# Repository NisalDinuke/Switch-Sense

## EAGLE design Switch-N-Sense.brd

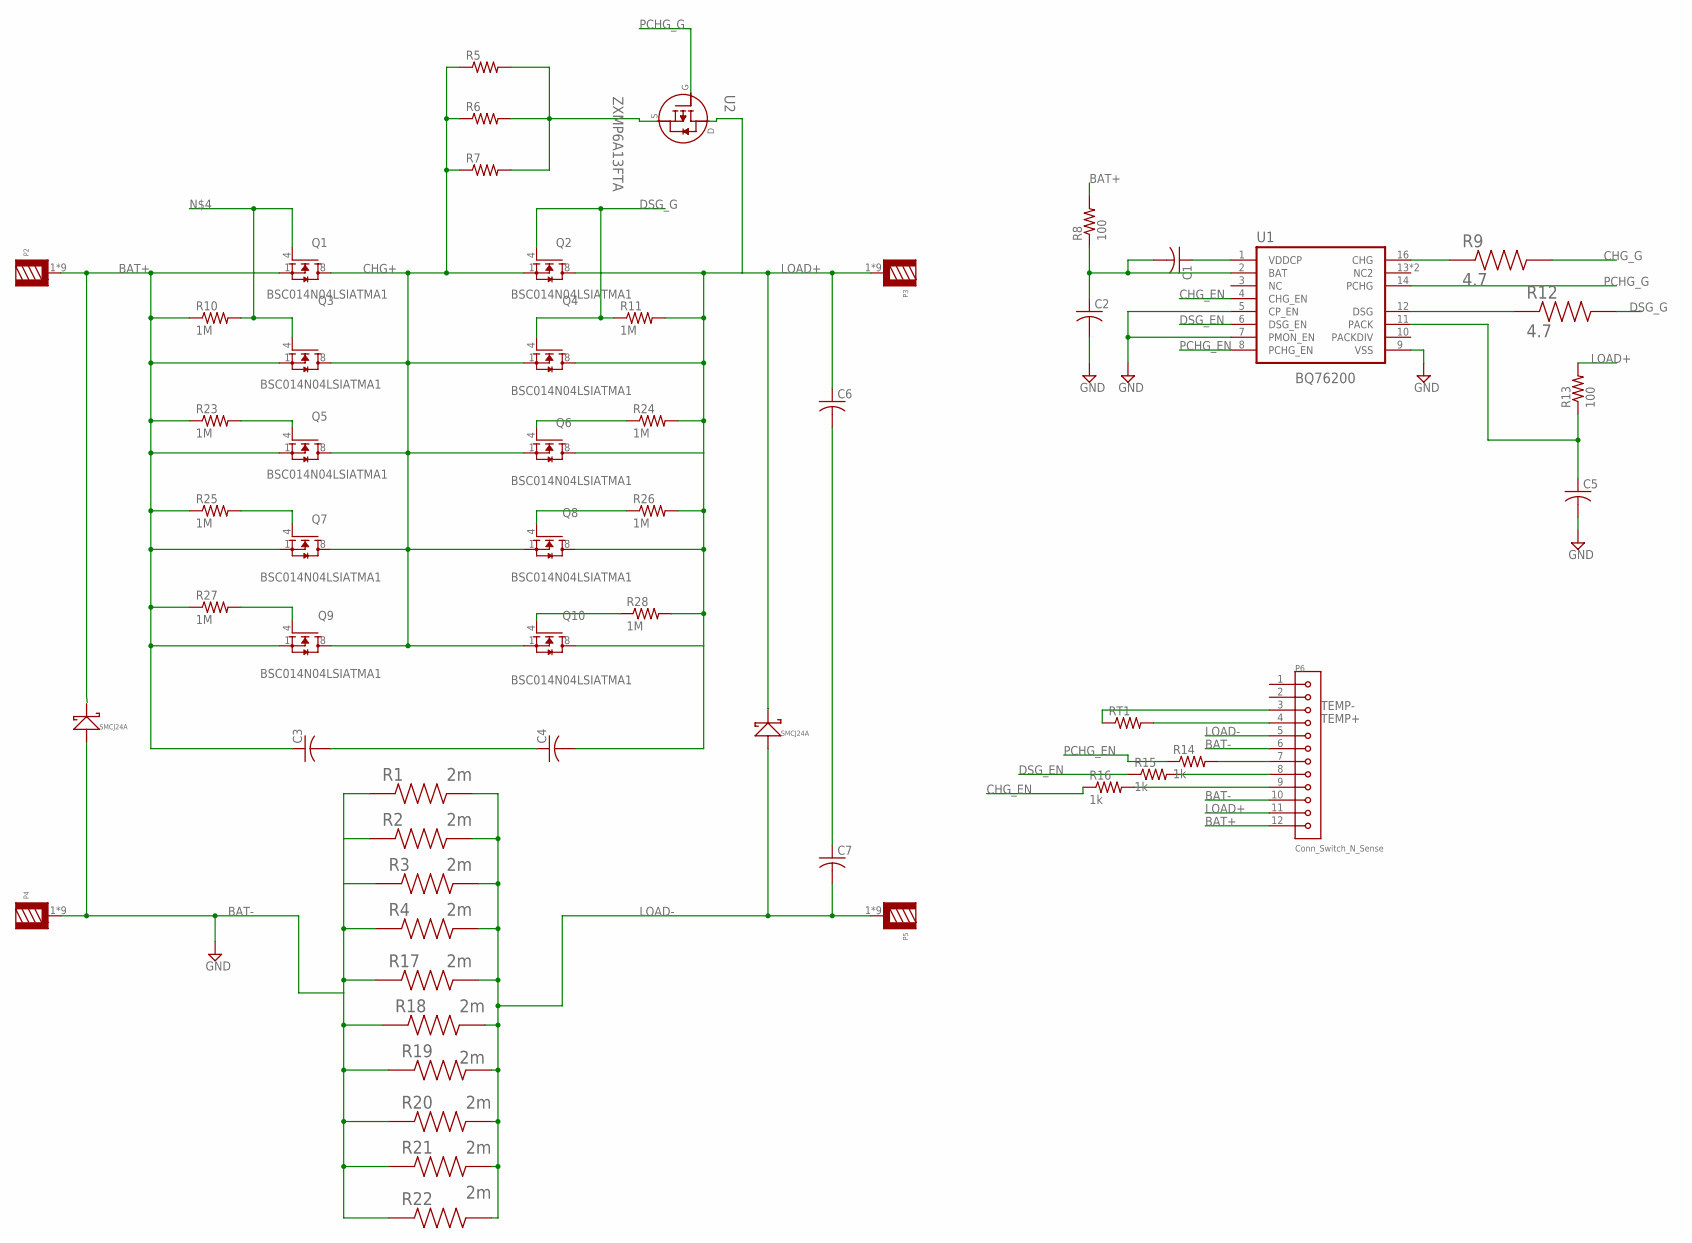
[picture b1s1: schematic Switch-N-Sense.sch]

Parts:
C1: C-USC0805; C0805
C2, C3, C4, C5, C6, C7: C-USC0603; C0603
D1, D2: SMCJ24A; DIOM794X590X262L114X305N
P2, P3, P4, P5: WP-THRBU_BLIND-HOLE_74650195; WP-THRBU_74650195
P6: Conn_Switch_N_Sense; JST_SM08B-SRSS-TB(LF)(SN)
Q1, Q2, Q3, Q4, Q5, Q6, Q7, Q8, Q9, Q10: BSC014N04LSIATMA1; TRANS_BSC014N04LSIATMA1
R1, R2, R3, R4, R17, R18, R19, R20, R21, R22: 2m; RESC6432X90N
R5, R6, R7: R-US_R5025; R5025
R8, R13: 100; R0603
R9, R12: 4.7; RESC1608X55N
R10, R11, R23, R24, R25, R26, R27, R28: 1M; R0603
R14, R15, R16: 1k; R0603
RT1: R-US_R0603; R0603
U1: MAX5135GUET; SOP65P640X110-16N
U2: ZXMP6A13FTA; SOT95P232X112-3N

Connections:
BAT+: C3.1, D1.1, P2.1, P2.2, P2.3, P2.4, P2.5, P2.6, P2.7, P2.8, P2.9, P6.12, Q1.1 (S), Q3.1 (S), Q5.1 (S), Q7.1 (S), Q9.1 (S), R8.2, R10.1, R23.1, R25.1, R27.1
BAT-: D1.2, P4.1, P4.2, P4.3, P4.4, P4.5, P4.6, P4.7, P4.8, P4.9, P6.6, P6.10, R1.1, R2.1, R3.1, R4.1, R17.1, R18.1, R19.1, R20.1, R21.1, R22.1
CHG+: Q1.8 (D), Q2.1 (S), Q3.8 (D), Q4.1 (S), Q5.8 (D), Q6.1 (S), Q7.8 (D), Q8.1 (S), Q9.8 (D), Q10.1 (S), R5.1, R6.1, R7.1
CHG_EN: R16.1, U1.4 (CHG_EN)
CHG_G: Q7.4 (G), R9.2, R25.2
DSG_EN: R15.1, U1.6 (DSG_EN)
DSG_G: Q2.4 (G), Q4.4 (G), R11.1, R12.2
GND: C2.2, C5.2, U1.5 (CP_EN), U1.7 (PMON_EN), U1.9 (VSS)
LOAD+: C4.2, C6.1, D2.1, P3.1, P3.2, P3.3, P3.4, P3.5, P3.6, P3.7, P3.8, P3.9, P6.11, Q2.8 (D), Q4.8 (D), Q6.8 (D), Q8.8 (D), Q10.8 (D), R11.2, R13.2, R24.2, R26.2, R28.2, U2.3 (D)
LOAD-: C7.2, D2.2, P5.1, P5.2, P5.3, P5.4, P5.5, P5.6, P5.7, P5.8, P5.9, P6.5, R1.2, R2.2, R3.2, R4.2, R17.2, R18.2, R19.2, R20.2, R21.2, R22.2
unnamed: R9.1, U1.16 (CHG)
unnamed: R12.1, U1.12 (DSG)
unnamed: C5.1, R13.1, U1.11 (PACK)
unnamed: Q1.4 (G), Q3.4 (G), R10.2
unnamed: Q5.4 (G), R23.2
unnamed: Q9.4 (G), R27.2
unnamed: Q10.4 (G), R28.1
unnamed: Q8.4 (G), R26.1
unnamed: Q6.4 (G), R24.1
unnamed: C1.1, U1.1 (VDDCP)
unnamed: C1.2, C2.1, R8.1, U1.2 (BAT)
unnamed: P6.7, R14.2
unnamed: P6.8, R15.2
unnamed: P6.9, R16.2
unnamed: C6.2, C7.1
unnamed: C3.2, C4.1
unnamed: R5.2, R6.2, R7.2, U2.2 (S)
PCHG_EN: R14.1, U1.8 (PCHG_EN)
PCHG_G: U1.14 (PCHG), U2.1 (G)
TEMP+: P6.4, RT1.2
TEMP-: P6.3, RT1.1

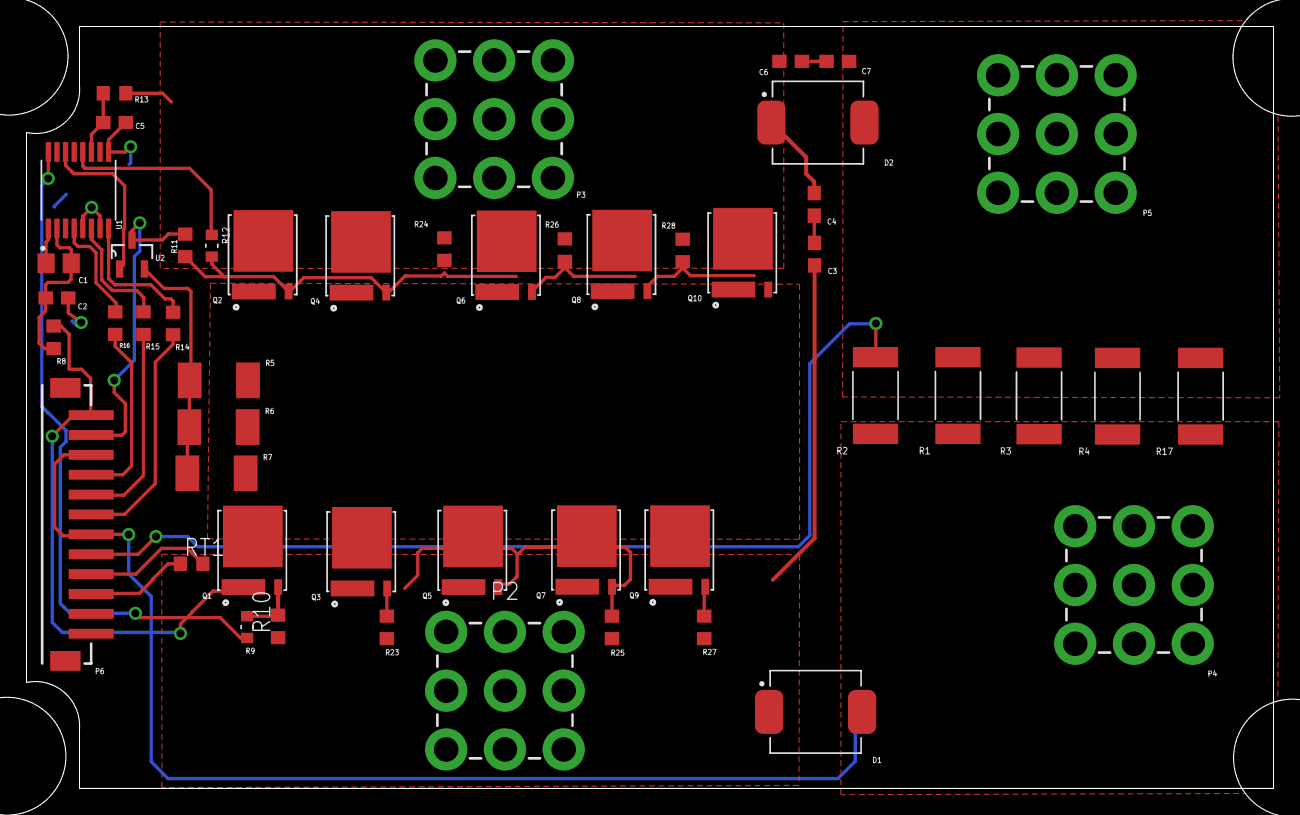
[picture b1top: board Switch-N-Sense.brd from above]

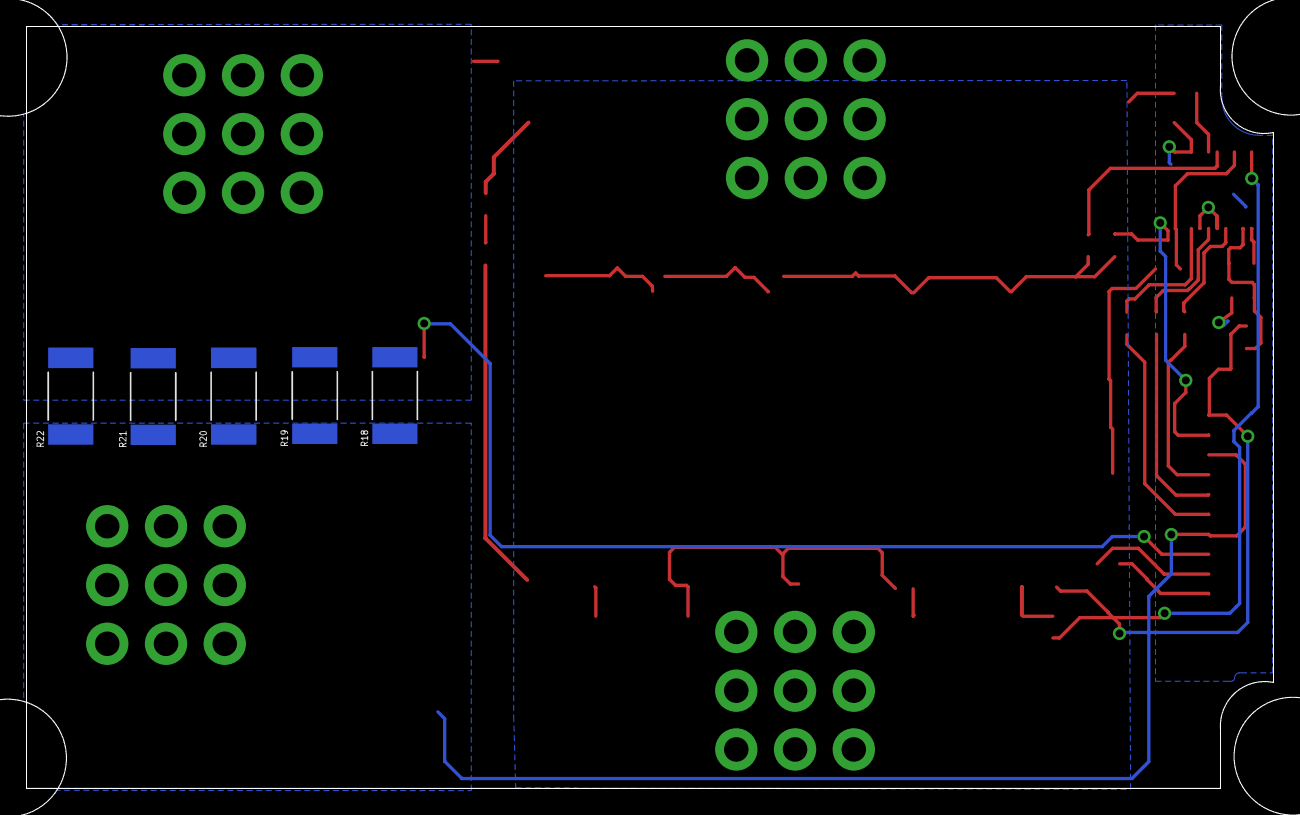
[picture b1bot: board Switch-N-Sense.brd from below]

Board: 2 copper layers, 94.1 x 57.5 mm, 55 parts (5 on the bottom side), 31 nets.

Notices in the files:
parts and their libraries:
74650094_Eagle_WP-THRBU_rev19a: Copyright: Würth Elektronik
